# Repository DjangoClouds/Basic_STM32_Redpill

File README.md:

# Basic STM32 Redpill Based Board

KiCAD PCB Design based on the STM32 Bluepill. Done with guidance from Phil's Lab STM32 PCB Design Tutorial from [Youtube](https://www.youtube.com/watch?v=aVUqaB0IMh4).
This version has been adjusted to incorporate a Raspberry Pi compatable header, two stepper motor drivers and a larger STM32 IC. It is, obviously, somewhat larger.

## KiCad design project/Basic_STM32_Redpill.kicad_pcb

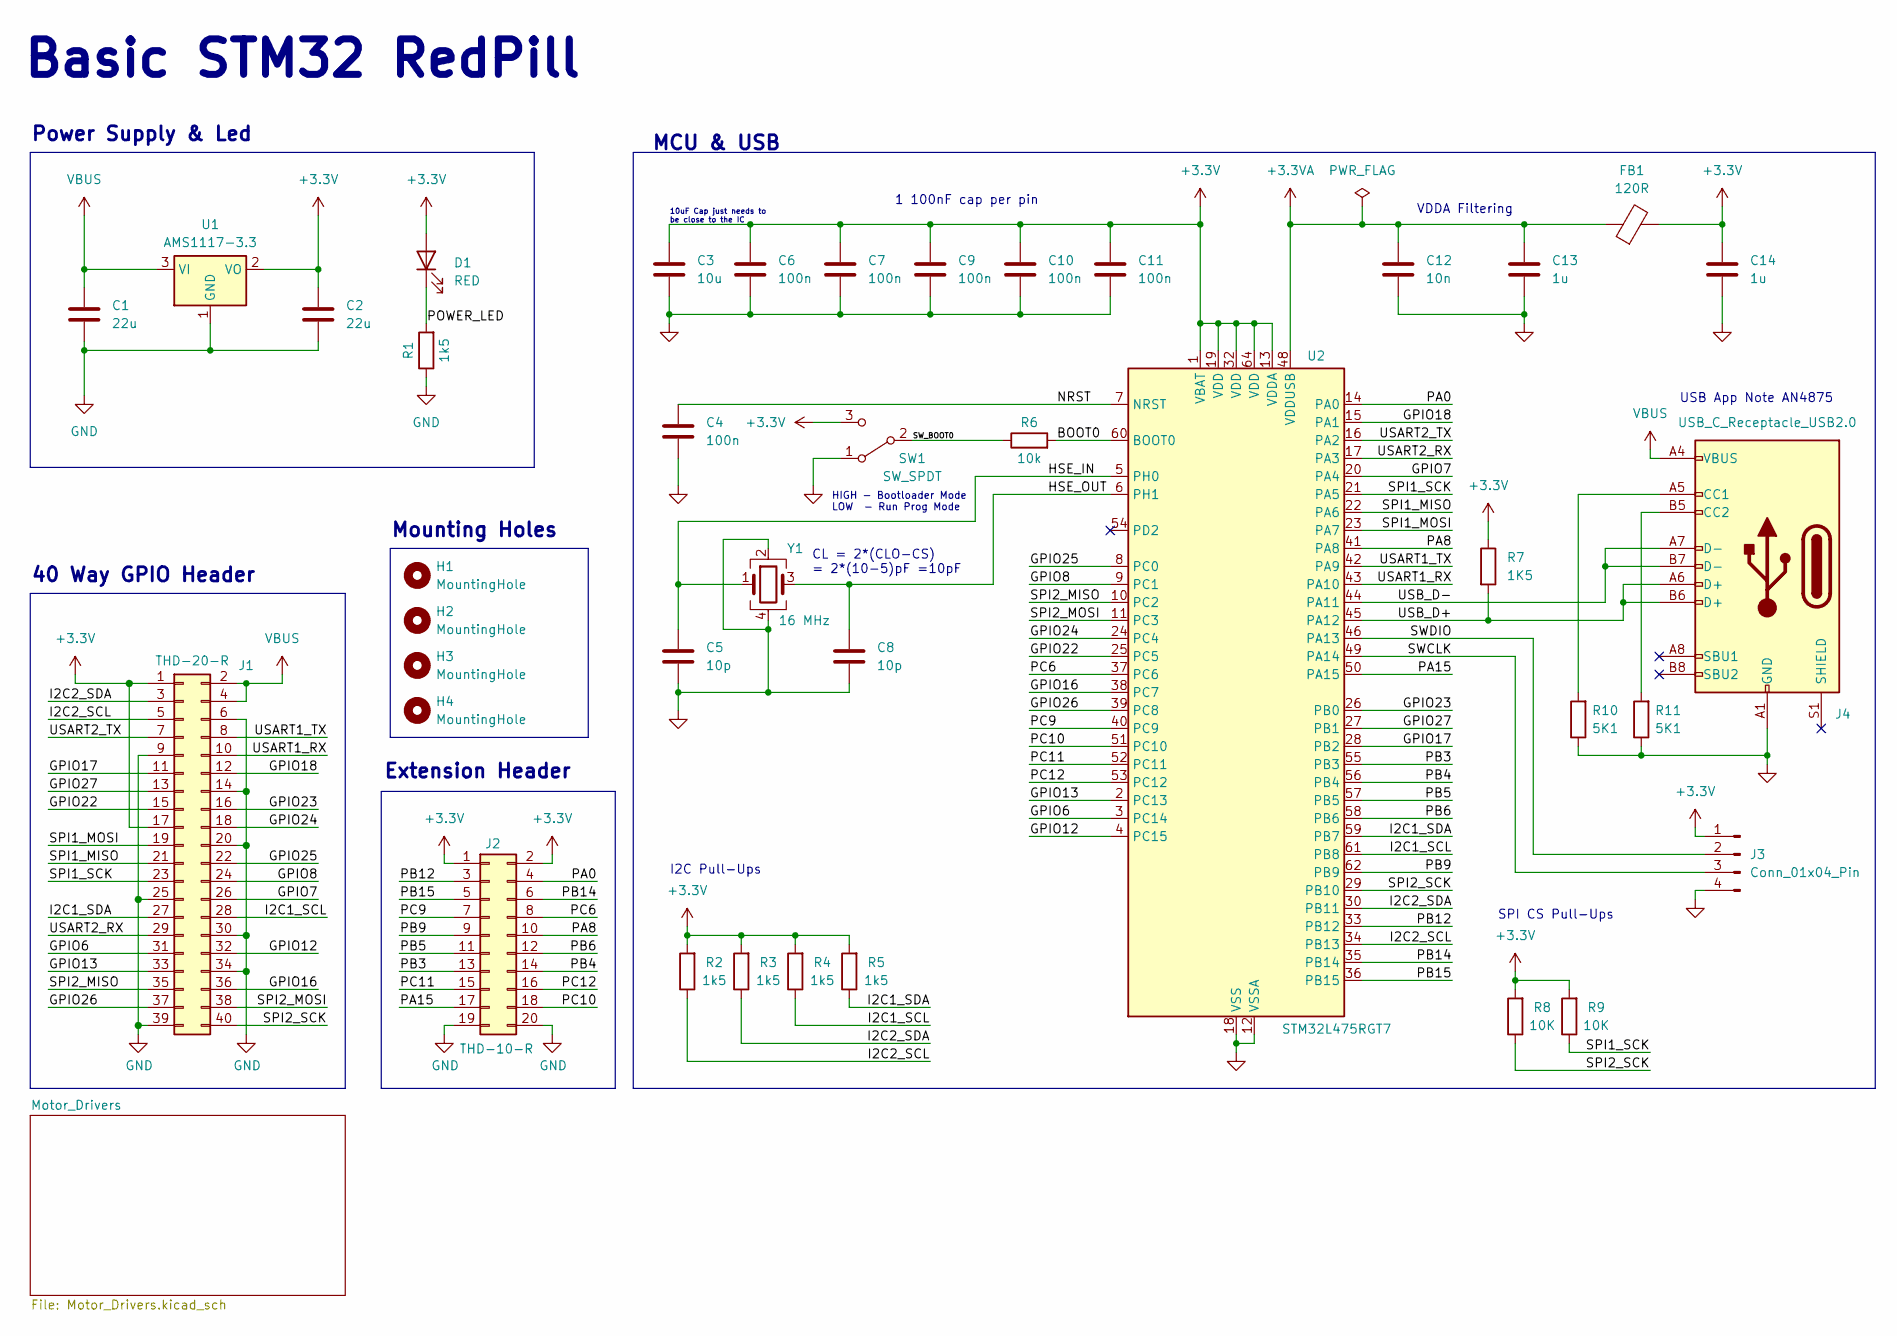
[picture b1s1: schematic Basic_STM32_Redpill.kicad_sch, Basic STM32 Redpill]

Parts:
C1, C2: 22u; C_0805_2012Metric
C3: 10u; C_0603_1608Metric
C4, C6, C7, C9, C10, C11: 100n; C_0402_1005Metric
C5, C8: 10p; C_0402_1005Metric
C12: 10n; C_0402_1005Metric
C13, C14: 1u; C_0402_1005Metric
D1: RED; LED_0603_1608Metric
FB1: 120R; L_0603_1608Metric
H1, H2, H3, H4: MountingHole; MountingHole_2.7mm_M2.5
J1: THD-20-R; PinHeader_2x20_P2.54mm_Vertical; Part Description PinHeader_2x20_P2.54mm_Vertical
J2: THD-10-R; PinHeader_2x10_P2.54mm_Vertical; Part Description PinHeader_2x20_P2.54mm_Vertical
J3: Conn_01x04_Pin; PinHeader_1x04_P2.54mm_Vertical
J4: USB_C_Receptacle_USB2.0; USB_C_Receptacle_GCT_USB4105-xx-A_16P_TopMnt_Horizontal; Part Description USBC USB2 data and power connector
R1, R2, R3, R4, R5: 1k5; R_0402_1005Metric
R6: 10k; R_0402_1005Metric
R7: 1K5; R_0402_1005Metric
R8, R9: 10K; R_0402_1005Metric
R10, R11: 5K1; R_0402_1005Metric
SW1: SW_SPDT; SW_SPDT_PCM12
U1: AMS1117-3.3; SOT-223-3_TabPin2
U2: STM32L475RGT7; LQFP-64_10x10mm_P0.5mm
Y1: 16 MHz; Crystal_SMD_3225-4Pin_3.2x2.5mm

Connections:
+3.3V: C2.1, C3.1, C6.1, C7.1, C9.1, C10.1, C11.1, C14.1, D1.2 (A), FB1.2, J1.1, J1.17, J2.1, J2.2, J3.1, R2.2, R3.2, R4.2, R5.2, R7.1, R8.2, R9.2, SW1.3 (C), U1.2 (VO), U2.1 (VBAT), U2.13 (VDDA), U2.19 (VDD), U2.32 (VDD), U2.64 (VDD); also elsewhere on the board
+3.3VA: C12.1, C13.1, FB1.1, U2.48 (VDDUSB)
/BOOT0: R6.2, U2.60 (BOOT0)
/GPIO6: J1.31, U2.3 (PC14)
/GPIO7: J1.26, U2.20 (PA4)
/GPIO8: J1.24, U2.9 (PC1)
/GPIO12: J1.32, U2.4 (PC15)
/GPIO13: J1.33, U2.2 (PC13)
/GPIO16: J1.36, U2.38 (PC7)
/GPIO17: J1.11, U2.28 (PB2)
/GPIO18: J1.12, U2.15 (PA1)
/GPIO22: J1.15, U2.25 (PC5)
/GPIO23: J1.16, U2.26 (PB0)
/GPIO24: J1.18, U2.24 (PC4)
/GPIO25: J1.22, U2.8 (PC0)
/GPIO26: J1.37, U2.39 (PC8)
/GPIO27: J1.13, U2.27 (PB1)
/HSE_IN: C5.1, U2.5 (PH0), Y1.1
/HSE_OUT: C8.1, U2.6 (PH1), Y1.3
/I2C1_SCL: J1.28, R4.1, U2.61 (PB8)
/I2C1_SDA: J1.27, R5.1, U2.59 (PB7)
/I2C2_SCL: J1.5, R2.1, U2.34 (PB13)
/I2C2_SDA: J1.3, R3.1, U2.30 (PB11)
/NRST: C4.1, U2.7 (NRST)
/PA0: J2.4, U2.14 (PA0)
/PA8: J2.10, U2.41 (PA8)
/PA15: J2.17, U2.50 (PA15)
/PB3: J2.13, U2.55 (PB3)
/PB4: J2.14, U2.56 (PB4)
/PB5: J2.11, U2.57 (PB5)
/PB6: J2.12, U2.58 (PB6)
/PB9: J2.9, U2.62 (PB9)
/PB12: J2.3, U2.33 (PB12)
/PB14: J2.6, U2.35 (PB14)
/PB15: J2.5, U2.36 (PB15)
/PC6: J2.8, U2.37 (PC6)
/PC9: J2.7, U2.40 (PC9)
/PC10: J2.18, U2.51 (PC10)
/PC11: J2.15, U2.52 (PC11)
/PC12: J2.16, U2.53 (PC12)
/POWER_LED: D1.1 (K), R1.2
/SPI1_MISO: J1.21, U2.22 (PA6)
/SPI1_MOSI: J1.19, U2.23 (PA7)
/SPI1_SCK: J1.23, R9.1, U2.21 (PA5)
/SPI2_MISO: J1.35, U2.10 (PC2)
/SPI2_MOSI: J1.38, U2.11 (PC3)
/SPI2_SCK: J1.40, R8.1, U2.29 (PB10)
/SWCLK: J3.3, U2.49 (PA14)
/SWDIO: J3.2, U2.46 (PA13)
/SW_BOOT0: R6.1, SW1.2 (B)
/USART1_RX: J1.10, U2.43 (PA10)
/USART1_TX: J1.8, U2.42 (PA9)
/USART2_RX: J1.29, U2.17 (PA3)
/USART2_TX: J1.7, U2.16 (PA2)
/USB_D+: J4.A6 (D+), J4.B6 (D+), R7.2, U2.45 (PA12)
/USB_D-: J4.A7 (D-), J4.B7 (D-), U2.44 (PA11)
GND: C1.2, C2.2, C3.2, C4.2, C5.2, C6.2, C7.2, C8.2, C9.2, C10.2, C11.2, C12.2, C13.2, C14.2, J1.6, J1.9, J1.14, J1.20, J1.25, J1.30, J1.34, J1.39, J2.19, J2.20, J3.4, J4.A1 (GND), J4.A12 (GND), J4.B1 (GND), J4.B12 (GND), R1.1, R10.1, R11.1, SW1.1 (A), U1.1 (GND), U2.12 (VSSA), U2.18 (VSS), U2.31 (VSS), U2.47 (VSS), U2.63 (VSS), Y1.2, Y1.4; also elsewhere on the board
unnamed: J4.A5 (CC1), R10.2
unnamed: J4.B5 (CC2), R11.2
VBUS: C1.1, J1.2, J1.4, J4.A4 (VBUS), J4.A9 (VBUS), J4.B4 (VBUS), J4.B9 (VBUS), U1.3 (VI)

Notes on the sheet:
Power Supply & Led
Mounting Holes
I2C Pull-Ups
USB App Note AN4875
10uF Cap just needs to be close to the IC
HIGH - Bootloader Mode LOW - Run Prog Mode
Extension Header
40 Way GPIO Header
SPI CS Pull-Ups
VDDA Filtering
CL = 2*(CLO-CS) = 2*(10-5)pF =10pF
Basic STM32 RedPill
MCU & USB
1 100nF cap per pin

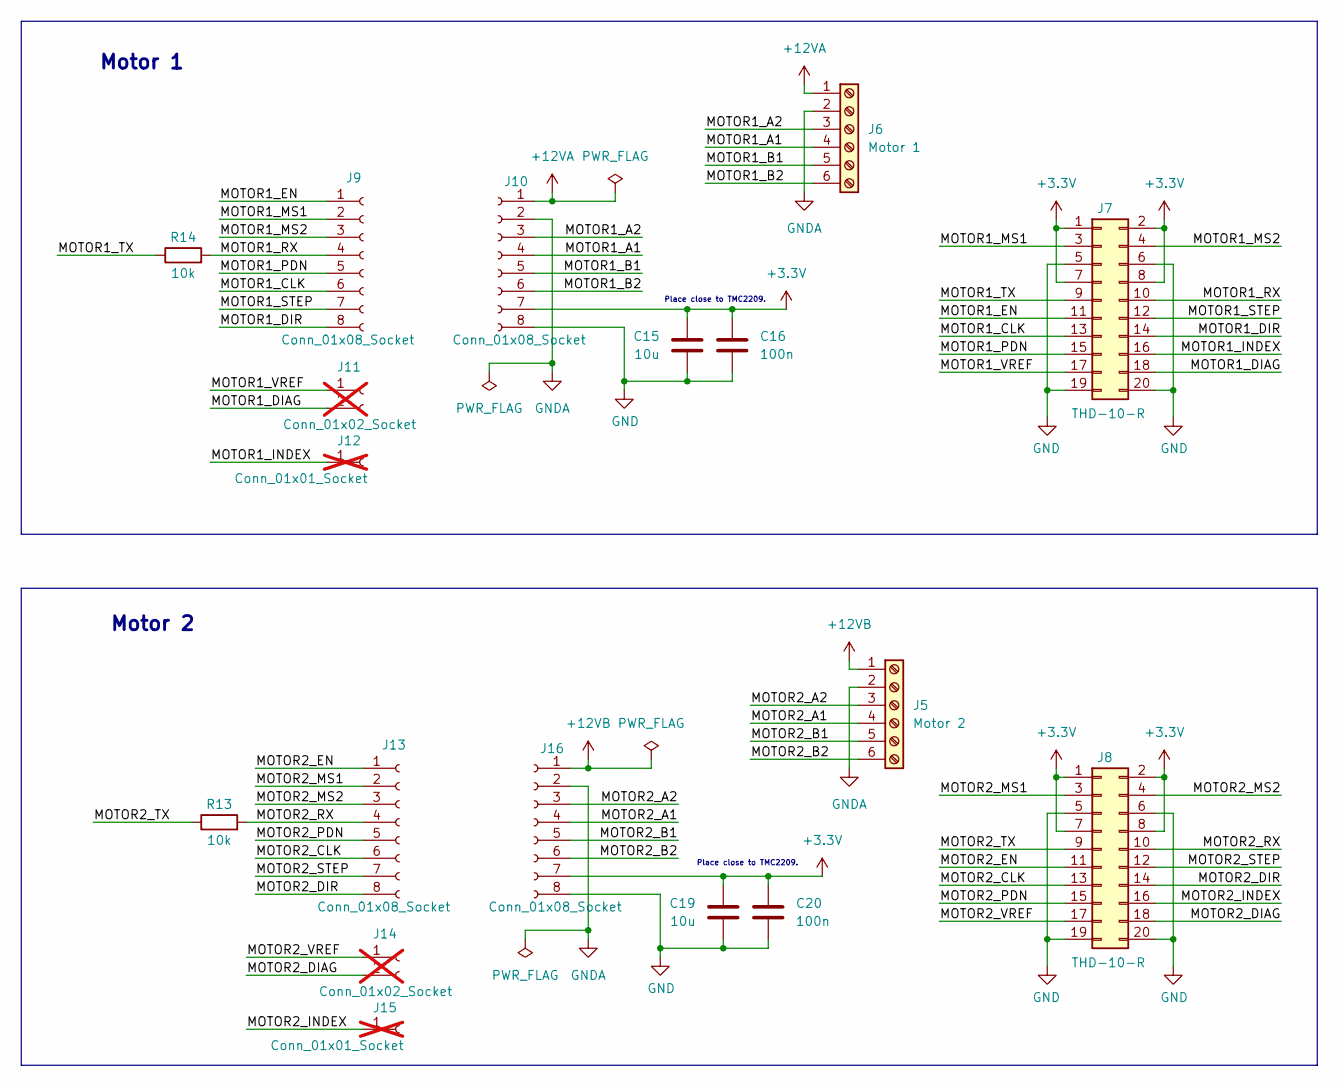
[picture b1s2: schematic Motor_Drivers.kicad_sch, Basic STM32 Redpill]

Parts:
C15, C19: 10u; C_0603_1608Metric
C16, C20: 100n; C_0402_1005Metric
J5: Motor 2; TerminalBlock_Xinya_XY308-2.54-6P_1x06_P2.54mm_Horizontal
J6: Motor 1; TerminalBlock_Xinya_XY308-2.54-6P_1x06_P2.54mm_Horizontal
J7, J8: THD-10-R; PinHeader_2x10_P2.54mm_Vertical; Part Description PinHeader_2x20_P2.54mm_Vertical
J9, J10, J13, J16: Conn_01x08_Socket; PinSocket_1x08_P2.54mm_Vertical
J11, J14: Conn_01x02_Socket; PinSocket_1x02_P2.54mm_Vertical; not fitted
J12, J15: Conn_01x01_Socket; PinSocket_1x01_P2.54mm_Vertical; not fitted
R13, R14: 10k; R_0402_1005Metric

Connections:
+3.3V: C15.1, C16.1, C19.1, C20.1, J7.1, J7.2, J7.7, J7.8, J8.1, J8.2, J8.7, J8.8, J10.7, J16.7; also elsewhere on the board
+12VA: J6.1, J10.1
+12VB: J5.1, J16.1
/Motor_Drivers/MOTOR1_A1: J6.4, J10.4
/Motor_Drivers/MOTOR1_A2: J6.3, J10.3
/Motor_Drivers/MOTOR1_B1: J6.5, J10.5
/Motor_Drivers/MOTOR1_B2: J6.6, J10.6
/Motor_Drivers/MOTOR1_CLK: J7.13, J9.6
/Motor_Drivers/MOTOR1_DIAG: J7.18, J11.2
/Motor_Drivers/MOTOR1_DIR: J7.14, J9.8
/Motor_Drivers/MOTOR1_EN: J7.11, J9.1
/Motor_Drivers/MOTOR1_INDEX: J7.16, J12.1
/Motor_Drivers/MOTOR1_MS1: J7.3, J9.2
/Motor_Drivers/MOTOR1_MS2: J7.4, J9.3
/Motor_Drivers/MOTOR1_PDN: J7.15, J9.5
/Motor_Drivers/MOTOR1_RX: J7.10, J9.4, R14.2
/Motor_Drivers/MOTOR1_STEP: J7.12, J9.7
/Motor_Drivers/MOTOR1_TX: J7.9, R14.1
/Motor_Drivers/MOTOR1_VREF: J7.17, J11.1
/Motor_Drivers/MOTOR2_A1: J5.4, J16.4
/Motor_Drivers/MOTOR2_A2: J5.3, J16.3
/Motor_Drivers/MOTOR2_B1: J5.5, J16.5
/Motor_Drivers/MOTOR2_B2: J5.6, J16.6
/Motor_Drivers/MOTOR2_CLK: J8.13, J13.6
/Motor_Drivers/MOTOR2_DIAG: J8.18, J14.2
/Motor_Drivers/MOTOR2_DIR: J8.14, J13.8
/Motor_Drivers/MOTOR2_EN: J8.11, J13.1
/Motor_Drivers/MOTOR2_INDEX: J8.16, J15.1
/Motor_Drivers/MOTOR2_MS1: J8.3, J13.2
/Motor_Drivers/MOTOR2_MS2: J8.4, J13.3
/Motor_Drivers/MOTOR2_PDN: J8.15, J13.5
/Motor_Drivers/MOTOR2_RX: J8.10, J13.4, R13.2
/Motor_Drivers/MOTOR2_STEP: J8.12, J13.7
/Motor_Drivers/MOTOR2_TX: J8.9, R13.1
/Motor_Drivers/MOTOR2_VREF: J8.17, J14.1
GND: C15.2, C16.2, C19.2, C20.2, J7.5, J7.6, J7.19, J7.20, J8.5, J8.6, J8.19, J8.20, J10.8, J16.8; also elsewhere on the board
GNDA: J5.2, J6.2, J10.2, J16.2

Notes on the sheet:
Place close to TMC2209.
Motor 2
Motor 1

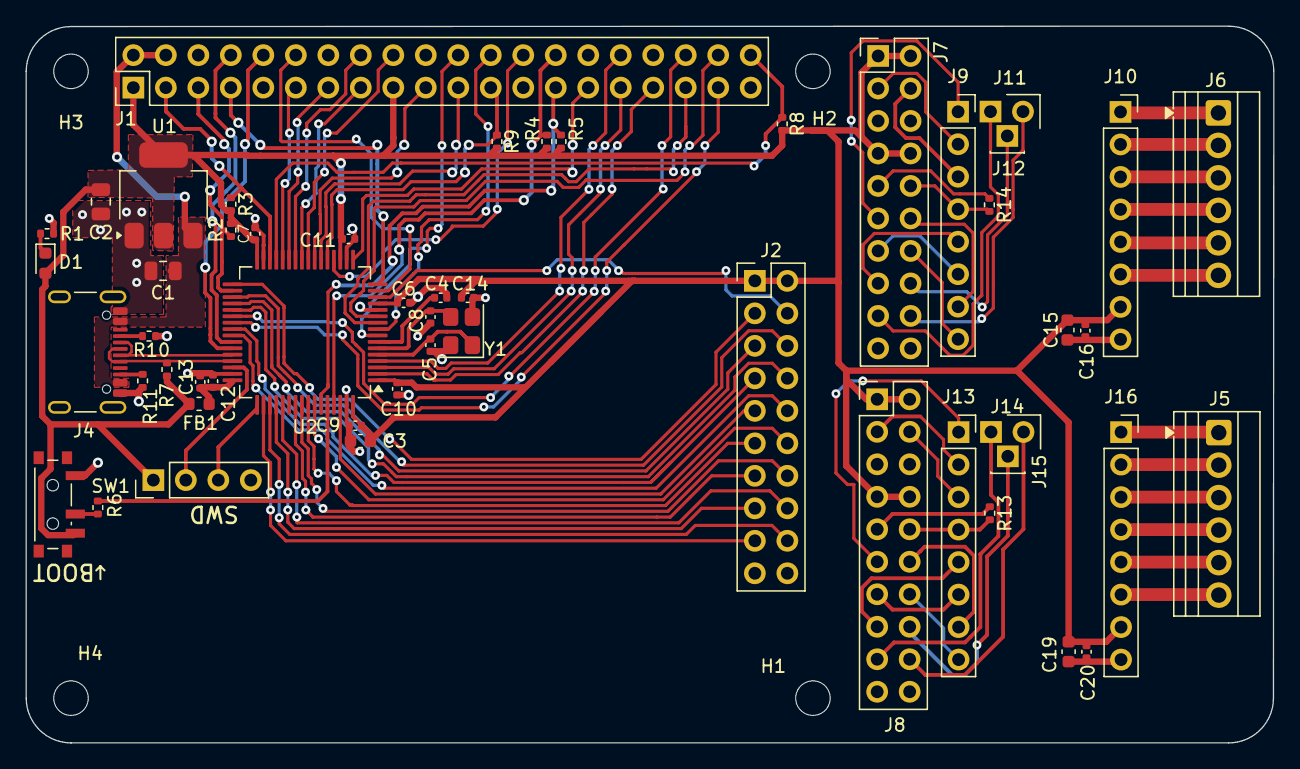
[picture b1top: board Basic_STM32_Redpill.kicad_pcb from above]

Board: 2 copper layers, 97.5 x 56.0 mm, 57 parts (0 on the bottom side), 95 nets.

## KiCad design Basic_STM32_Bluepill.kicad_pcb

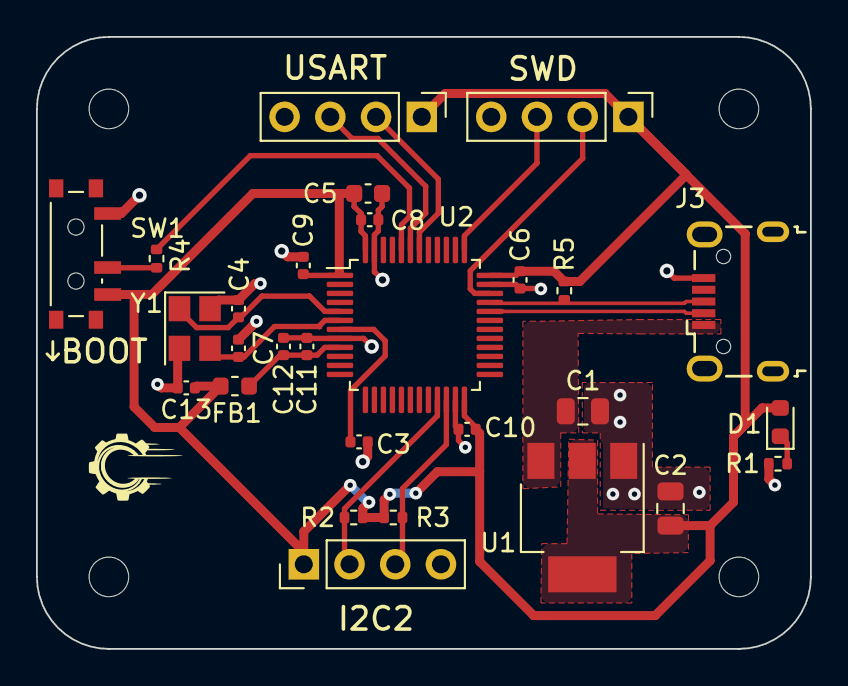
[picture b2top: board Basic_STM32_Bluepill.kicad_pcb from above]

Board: 2 copper layers, 43.0 x 34.0 mm, 32 parts (0 on the bottom side), 18 nets.

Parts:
C1, C2: 22u; C_0805_2012Metric
C3, C6, C8, C9, C10: 100n; C_0402_1005Metric
C4, C7: 10p; C_0402_1005Metric
C5: 10u; C_0603_1608Metric
C11: 10n; C_0402_1005Metric
C12, C13: 1u; C_0402_1005Metric
D1: RED; LED_0603_1608Metric
FB1: 120R; L_0603_1608Metric
H1, H2, H3, H4: MountingHole; MountingHole_2.2mm_M2
J1, J2, J4: Conn_01x04_Pin; PinHeader_1x04_P2.54mm_Vertical
J3: USB_B_Micro; USB_Micro-B_Wuerth_629105150521
R1, R2, R3: 1k5; R_0402_1005Metric
R4: 10k; R_0402_1005Metric
R5: 1K5; R_0402_1005Metric
SW1: SW_SPDT; SW_SPDT_PCM12
U1: AMS1117-3.3; SOT-223-3_TabPin2
U2: STM32F103C8T6; LQFP-48_7x7mm_P0.5mm
Y1: 16 MHz; Crystal_SMD_3225-4Pin_3.2x2.5mm

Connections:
+3.3V: C2.1, C5.1, C6.1, C8.1, C9.1, C10.1, C13.1, D1.2 (A), FB1.2, J1.1, J2.1, J4.1, R2.2, R3.2, R5.1, SW1.3 (C), U1.2 (VO), U2.1 (VBAT), U2.24 (VDD), U2.36 (VDD), U2.48 (VDD)
+3.3VA: C11.1, C12.1, FB1.1, U2.9 (VDDA)
/BOOT0: R4.2, U2.44 (BOOT0)
/HSE_IN: C4.1, U2.5 (PD0), Y1.1
/HSE_OUT: C7.1, U2.6 (PD1), Y1.3
/I2C2_SCL: J1.2, R2.1, U2.21 (PB10)
/I2C2_SDA: J1.3, R3.1, U2.22 (PB11)
/NRST: C3.1, U2.7 (NRST)
/POWER_LED: D1.1 (K), R1.2
/SWCLK: J4.3, U2.37 (PA14)
/SWDIO: J4.2, U2.34 (PA13)
/SW_BOOT0: R4.1, SW1.2 (B)
/USART1_RX: J2.3, U2.43 (PB7)
/USART1_TX: J2.2, U2.42 (PB6)
/USB_D+: J3.3 (D+), R5.2, U2.33 (PA12)
/USB_D-: J3.2 (D-), U2.32 (PA11)
GND: C1.2, C2.2, C3.2, C4.2, C5.2, C6.2, C7.2, C8.2, C9.2, C10.2, C11.2, C12.2, C13.2, J1.4, J2.4, J3.5 (GND), J4.4, R1.1, SW1.1 (A), U1.1 (GND), U2.8 (VSSA), U2.23 (VSS), U2.35 (VSS), U2.47 (VSS), Y1.2, Y1.4
VBUS: C1.1, J3.1 (VBUS), U1.3 (VI)

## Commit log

2023-12-07 first upload
2023-12-07 rearrange, add schematic to README
2025-06-16 First draft of changes
    Added the RPi style connector and an extra for remaining pins.
2025-06-23 Schematic and layout done.
    Need to double check it &n generate the BOM and gerbers.
